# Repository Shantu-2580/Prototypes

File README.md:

<div align="center">

# ⚡ Prototypes

### Electronics • Embedded Systems • Robotics • PCB Design

*"Where ideas become circuits before they become products."*

</div>

---

# About

This repository contains my collection of hardware and embedded engineering prototypes.

Instead of polished end products, this repository documents experiments, PCB designs, robotics projects, firmware, and proof-of-concepts developed while exploring electronics and embedded systems.

Some projects are complete.

Some are works in progress.

Every project contributes to learning.

---

# Repository Structure

```text
Prototypes
│
├── ESP
│   │
│   ├── LM358_Audio_Input_Sensor
│   │   ├── KiCad PCB
│   │   ├── Schematic
│   │   └── Images
│   │
│   ├── Self_Balancing_Bot
│   │   ├── PCB
│   │   ├── Schematic
│   │   └── Arduino Code
│   │
│   ├── controller_sense
│   │   ├── Physical Controller Test
│   │   └── Virtual Controller Test
│   │
│   └── nexus_mascot_codes
│       └── Arduino Sketch
│
└── More prototypes coming soon...
```

---

# Current Projects

## 🎵 LM358 Audio Input Sensor

Custom PCB designed in KiCad for audio signal sensing using the LM358 operational amplifier.

**Includes**

- PCB Design
- Schematic
- Project Files
- Hardware Images
- Prototype Video

---

## 🤖 Self Balancing Bot

A robotics prototype focused on balancing algorithms and embedded control.

**Includes**

- KiCad PCB
- Circuit Schematic
- Arduino Firmware
- Project Files

---

## 🎮 Controller Sense

Python utilities for testing controller inputs.

Includes both:

- Physical controller testing
- Virtual controller simulation

---

## 🛰️ NEXUS Mascot

Arduino sketches related to the NEXUS mascot prototype.

---

# Tools Used

- KiCad
- Arduino IDE
- ESP32 / Arduino
- Python
- Git

---

# Philosophy

Every finished project begins as an experiment.

This repository serves as my engineering notebook where ideas are explored, validated, and improved before becoming complete systems.

---

# Roadmap

Future additions may include:

- ESP32 Projects
- IoT Systems
- PCB Designs
- Robotics
- Embedded AI
- Sensor Networks
- Control Systems
- Hardware Testing Utilities

---

# Contributing

Suggestions, improvements, and discussions are always welcome.

Feel free to open an Issue or submit a Pull Request.

---

<div align="center">

**Designed & Maintained by**

### Shantanu Gaikwad

*"Build. Test. Iterate. Repeat."*

⭐ If you find these projects useful, consider starring the repository.

</div>

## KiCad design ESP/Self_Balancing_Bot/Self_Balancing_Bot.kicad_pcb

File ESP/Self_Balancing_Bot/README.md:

# Self-Balancing Bot

A two-wheeled self-balancing robot using ESP32, MPU6050 (accelerometer + gyroscope), TB6612FNG motor driver, and Bluetooth gamepad control via Bluepad32.

## Hardware Requirements

| Component | Notes |
|-----------|-------|
| ESP32 DevKit | 30+ GPIO pins |
| MPU6050 | I2C address 0x68 (SDA=21, SCL=22) |
| TB6612FNG | Dual H-bridge motor driver |
| 2x DC Motors | With encoder support (optional) |
| LiPo Battery | 2S-3S (7.4V-11.1V) with voltage regulator |
| Bluetooth Gamepad | Tested with Xbox/PS4/8BitDo controllers |

## Pinout

```
ESP32          TB6612FNG          MPU6050
────────────────────────────────────────────
GPIO 33   →    PWMA
GPIO 14   →    AIN1
GPIO 15   →    AIN2
GPIO 32   →    PWMB
GPIO 26   →    BIN1
GPIO 27   →    BIN2
GPIO 21   →    SDA
GPIO 22   →    SCL
3.3V      →    VCC
GND       →    GND
```

## Firmware Files

### `Codes/P1/P1.ino` — Original Version
**Status:** Reference implementation (has placeholder values)

**Features:**
- Basic PID balance control (100Hz loop)
- Complementary filter for sensor fusion (MPU6050 accel + gyro)
- Bluetooth gamepad control via Bluepad32
- TB6612FNG motor driver interface
- Fall detection safety cutoff (>45°)

**Known Issues:**
- ❌ `Kp`, `Ki`, `Kd`, `base_setpoint` set to `Add_Values_Later` — **won't compile**
- ❌ No calibration routine — `base_setpoint` must be manually tuned per robot
- ❌ No integral anti-windup — causes overshoot after disturbances
- ❌ No motor deadband compensation — motors stall at low PWM
- ❌ No gamepad deadzone — joystick drift causes unwanted movement
- ❌ No controller watchdog — robot keeps moving if controller dies
- ❌ No MPU6050 verification — silent failure if sensor disconnected
- ❌ No serial telemetry — blind PID tuning

---

### `Codes/P1/Program2.ino` — Optimized Version
**Status:** Production-ready with all fixes

**All Original Features Plus:**

| Category | Improvements |
|----------|--------------|
| **Compilable** | Real PID defaults: `Kp=25.0`, `Ki=0.8`, `Kd=1.2` |
| **Calibration** | 2-second startup routine averages accelerometer to find `base_setpoint` automatically |
| **Anti-Windup** | Dual protection: integral clamped at ±400 + integration pauses when output saturates (±255) |
| **Motor Deadband** | `MIN_PWM=25` ensures TB6612FNG overcomes static friction |
| **Gamepad Deadzone** | Ignores joystick input < 20 (prevents center drift) |
| **Watchdog** | Auto-stops motors if controller disconnects >500ms |
| **Sensor Verify** | Checks WHO_AM_I register (0x68) at startup, halts if missing |
| **DLPF Config** | Hardware low-pass filter set to 44Hz (accel) / 42Hz (gyro) |
| **Telemetry** | 1Hz serial output: angle, setpoint, PID terms for tuning |
| **I2C Optimized** | Single 14-byte read transaction per loop |

---

## PID Tuning Guide (Program2)

Open Serial Monitor at **115200 baud**. You'll see:
```
Angle: 0.12 | Setpoint: 0.00 | Out: -15.3 | P: -3.0 I: -0.2 D: -12.1
```

### Tuning Order:
1. **Kp only** (set `Ki=0, Kd=0`): Increase until sustained oscillation, then reduce ~30%
2. **Kd**: Add to dampen oscillations (start ~0.5-2.0)
3. **Ki**: Small value (0.5-2.0) to eliminate steady-state drift

### Tips:
- Hold robot upright during 2-second calibration (LED on ESP32 blinks during this)
- Test on carpet first — smoother surface = easier balance
- If robot falls backward consistently, increase `base_setpoint` slightly (or add weight forward)
- `Kp` typically 20-50, `Kd` 0.5-3, `Ki` 0.5-2 for this hardware

---

## Building & Flashing

### Arduino IDE
1. Install ESP32 board package: `https://dl.espressif.com/dl/package_esp32_index.json`
2. Install **Bluepad32** library via Library Manager
3. Open `Program2.ino`, select board **ESP32 Dev Module**, upload

### PlatformIO (Recommended)
```ini
; platformio.ini
[env:esp32dev]
platform = espressif32
board = esp32dev
framework = arduino
lib_deps =
    ricardoquesada/Bluepad32 @ ^2.0.0
monitor_speed = 115200
```

---

## Troubleshooting

| Symptom | Likely Cause | Fix |
|---------|--------------|-----|
| Won't compile | Using `P1.ino` | Use `Program2.ino` |
| Falls immediately | PID not tuned | Follow tuning guide above |
| Drifts forward/back | Wrong `base_setpoint` | Re-calibrate (reset ESP32) |
| Oscillates violently | Kp too high / Kd too low | Reduce Kp, increase Kd |
| Slow to correct | Kp too low | Increase Kp |
| Motors hum but don't turn | Deadband too low | Increase `MIN_PWM` (try 30-40) |
| Controller doesn't pair | Bluepad32 keys stored | `BP32.forgetBluetoothKeys()` runs on startup |
| MPU6050 not detected | Wiring / I2C address | Check SDA/SCL, try 0x69 (AD0=HIGH) |

---

## License

MIT — Feel free to use, modify, distribute.

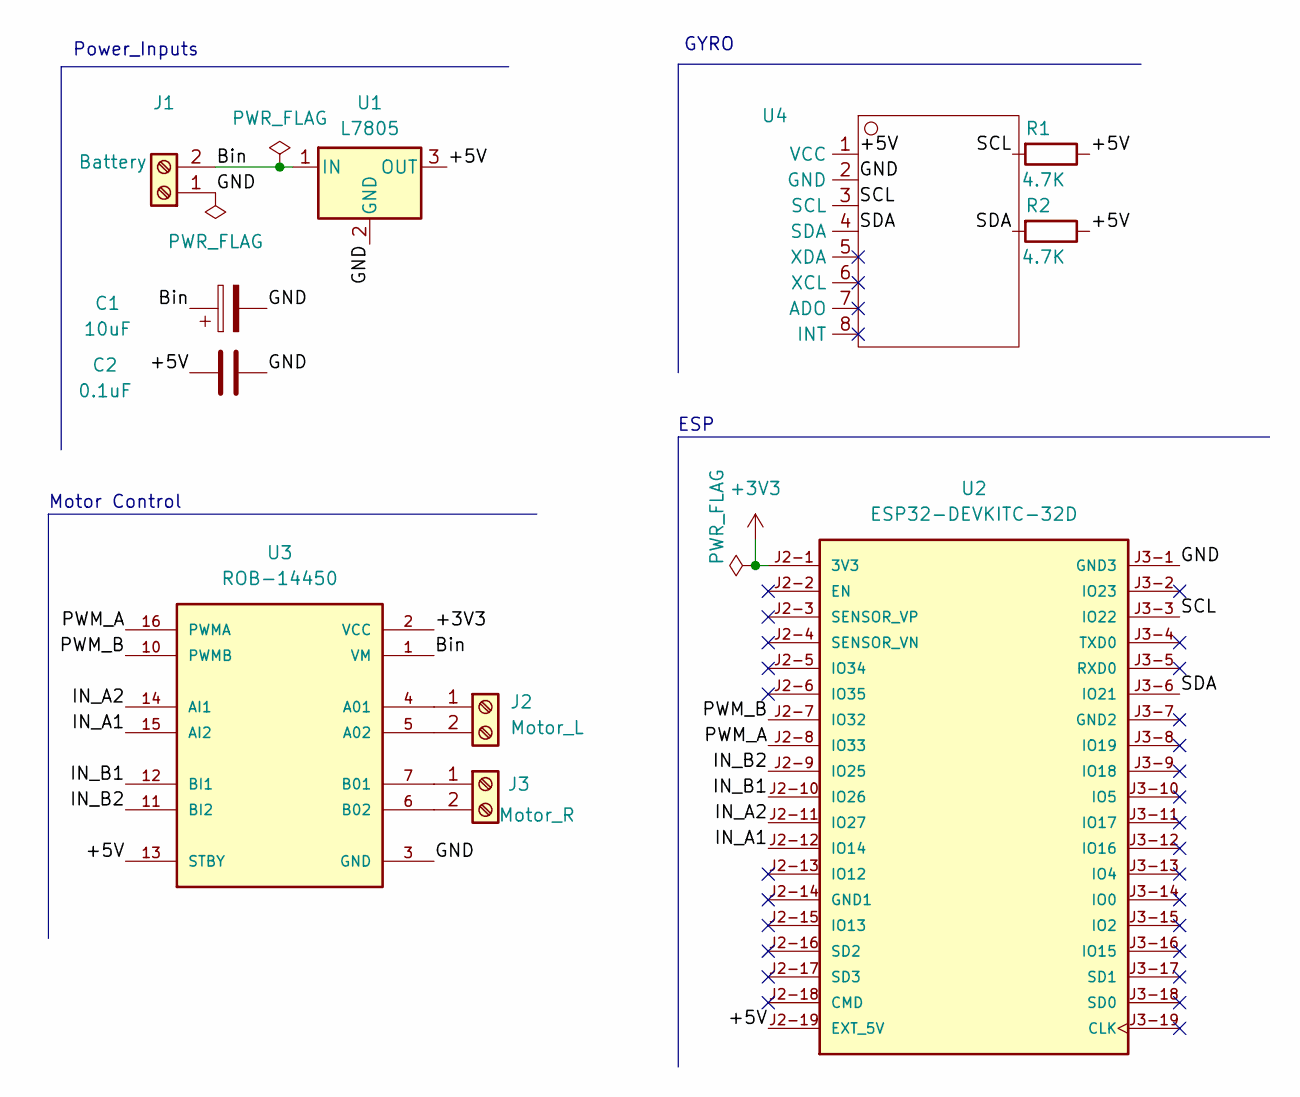
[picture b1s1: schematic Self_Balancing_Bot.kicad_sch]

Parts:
C1: 10uF; CP_Radial_D5.0mm_P2.00mm
C2: 0.1uF; CP_Radial_D5.0mm_P2.50mm
J1: Battery; PhoenixContact_MSTBA_2,5_2-G-5,08_1x02_P5.08mm_Horizontal
J2: Motor_L; PhoenixContact_MSTBA_2,5_2-G-5,08_1x02_P5.08mm_Horizontal
J3: Motor_R; PhoenixContact_MSTBA_2,5_2-G-5,08_1x02_P5.08mm_Horizontal
R1, R2: 4.7K; R_Axial_DIN0207_L6.3mm_D2.5mm_P7.62mm_Horizontal
U1: L7805; TO-220-3_Vertical
U2: ESP32-DEVKITC-32D; MODULE_ESP32-DEVKITC-32D; PARTREV V4
U3: ROB-14450; MODULE_ROB-14450; PARTREV 11-13-17
U4: Untitled

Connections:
+3V3: U2.J2-1 (3V3), U3.2 (VCC)
/+5V: C2.1, R1.1, R2.1, U1.3 (OUT), U2.J2-19 (EXT_5V), U3.13 (STBY), U4.1 (VCC)
/Bin: C1.1, J1.2, U1.1 (IN), U3.1 (VM)
/IN_A1: U2.J2-12 (IO14), U3.15 (AI2)
/IN_A2: U2.J2-11 (IO27), U3.14 (AI1)
/IN_B1: U2.J2-10 (IO26), U3.12 (BI1)
/IN_B2: U2.J2-9 (IO25), U3.11 (BI2)
/PWM_A: U2.J2-8 (IO33), U3.16 (PWMA)
/PWM_B: U2.J2-7 (IO32), U3.10 (PWMB)
/SCL: R1.2, U2.J3-3 (IO22), U4.3 (SCL)
/SDA: R2.2, U2.J3-6 (IO21), U4.4 (SDA)
GND: C1.2, C2.2, J1.1, U1.2 (GND), U2.J3-1 (GND3), U3.3 (GND), U3.8 (GND), U3.9 (GND), U4.2 (GND)
unnamed: J2.1, U3.4 (A01)
unnamed: J2.2, U3.5 (A02)
unnamed: J3.1, U3.7 (B01)
unnamed: J3.2, U3.6 (B02)

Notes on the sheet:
GYRO
ESP
Motor Control
Power_Inputs

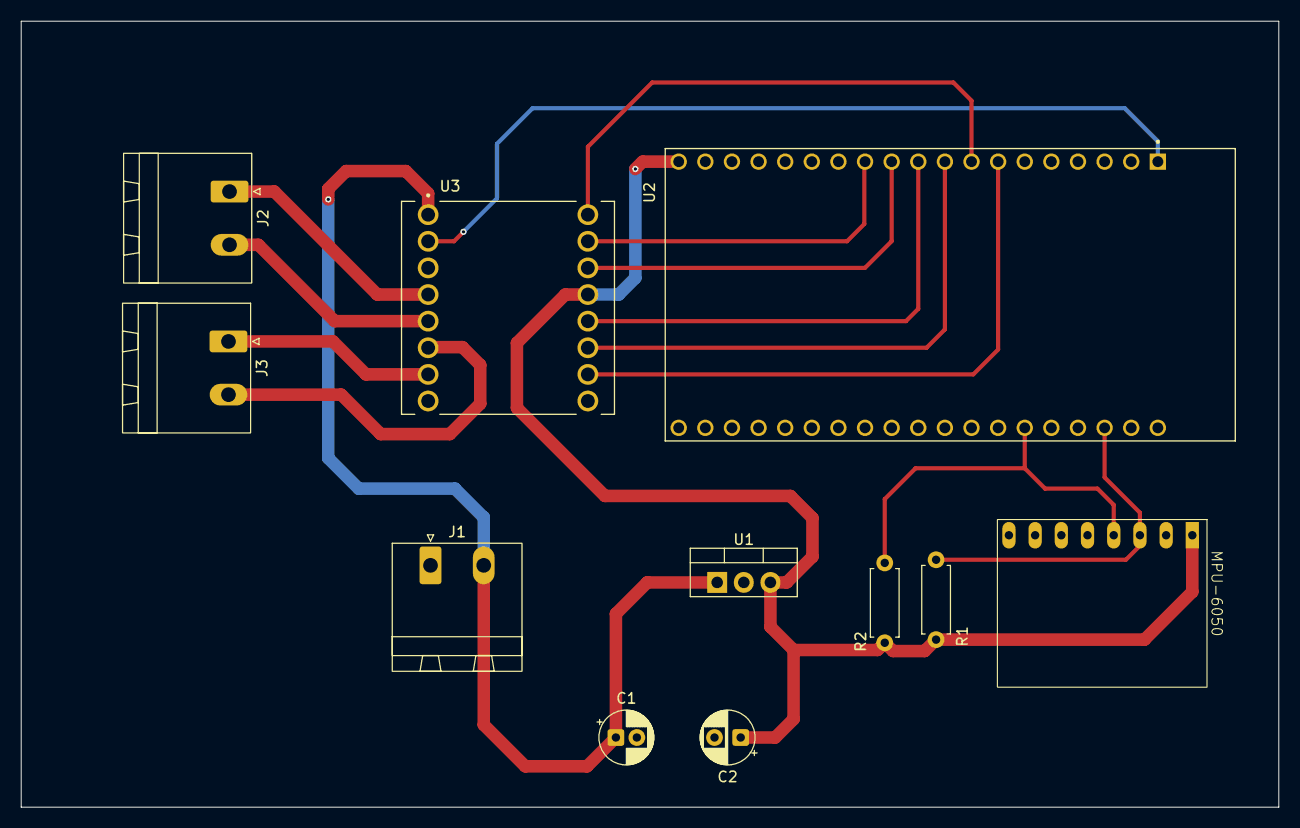
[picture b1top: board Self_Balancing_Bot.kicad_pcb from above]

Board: 2 copper layers, 120.0 x 75.0 mm, 11 parts (0 on the bottom side), 16 nets.

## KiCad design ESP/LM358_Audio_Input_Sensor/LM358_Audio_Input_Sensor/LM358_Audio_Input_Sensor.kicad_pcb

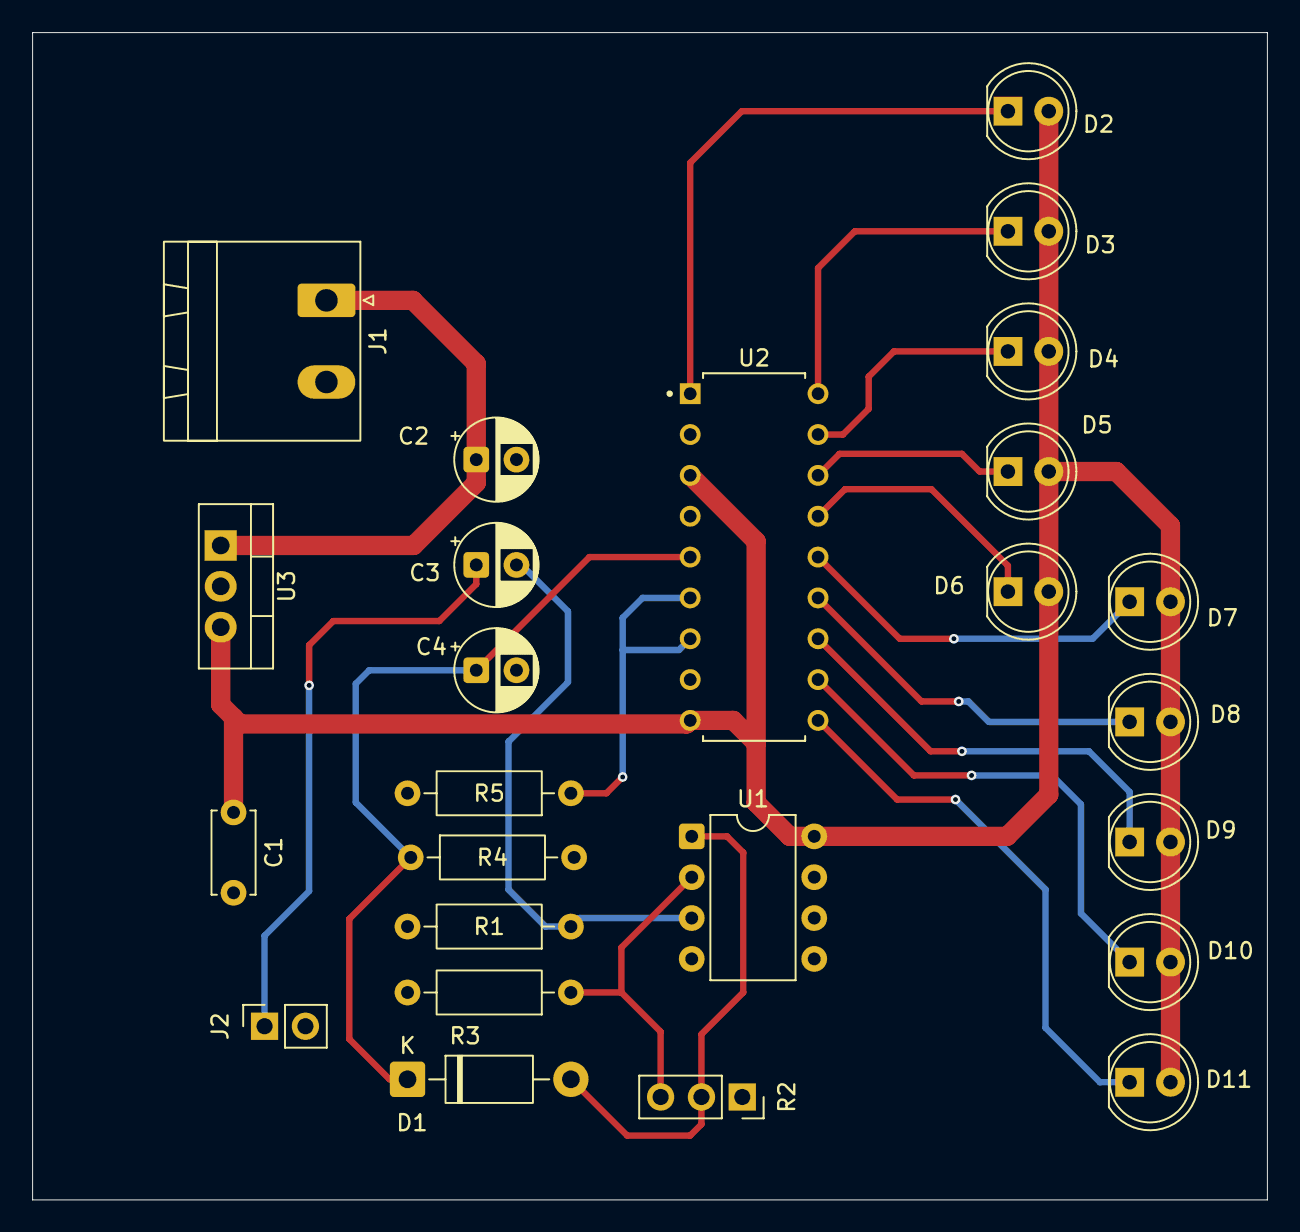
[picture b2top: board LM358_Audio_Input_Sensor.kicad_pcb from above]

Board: 2 copper layers, 76.8 x 72.6 mm, 25 parts (0 on the bottom side), 19 nets.

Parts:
C1: 100nF; C_Disc_D5.0mm_W2.5mm_P5.00mm
C2: 10uF; CP_Radial_D5.0mm_P2.50mm
C3, C4: 1uF; CP_Radial_D5.0mm_P2.50mm
D1: 1N4007; D_DO-41_SOD81_P10.16mm_Horizontal
D2, D3, D4, D5, D6, D7, D8, D9, D10, D11: LED; LED_D5.0mm
J1: Battery_in; PhoenixContact_MSTBA_2,5_2-G-5,08_1x02_P5.08mm_Horizontal
J2: Audio_in; PinSocket_1x02_P2.54mm_Vertical
R1, R3: 100k; R_Axial_DIN0207_L6.3mm_D2.5mm_P10.16mm_Horizontal
R2: Potentiometer; PinSocket_1x03_P2.54mm_Vertical
R4: 10k; R_Axial_DIN0207_L6.3mm_D2.5mm_P10.16mm_Horizontal
R5: 1.2k; R_Axial_DIN0207_L6.3mm_D2.5mm_P10.16mm_Horizontal
U1: DIP-8_W7.62mm
U2: LM3915; DIP795W45P254L2286H533Q18B
U3: L7805; TO-220-3_Vertical

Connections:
/+5V: C1.1, D2.2 (A), D3.2 (A), D4.2 (A), D5.2 (A), D6.2 (A), D7.2 (A), D8.2 (A), D9.2 (A), D10.2 (A), D11.2 (A), U1.8 (+Vcc), U2.3 (V+), U2.9 (MODE_SELECT), U3.3 (OUT)
/Fo: C4.1, D1.1 (K), R4.1, U2.5 (SIGNAL_INPUT)
/GND: C1.2, C2.2, C4.2, J1.2, J2.2, R1.2, R3.2, R4.2, R5.2, U1.4 (-VDD), U2.2 (V-), U2.4 (DIVIDER(LOW_END)), U2.8 (REFERENCE_ADJUST), U3.2 (GND)
/O1: D1.2 (A), R2.2, U1.1 (Out1)
unnamed: D2.1 (K), U2.1 (LED1)
unnamed: D3.1 (K), U2.18 (LED2)
unnamed: D4.1 (K), U2.17 (LED3)
unnamed: D5.1 (K), U2.16 (LED4)
unnamed: D6.1 (K), U2.15 (LED5)
unnamed: D7.1 (K), U2.14 (LED6)
unnamed: D8.1 (K), U2.13 (LED7)
unnamed: D9.1 (K), U2.12 (LED8)
unnamed: D10.1 (K), U2.11 (LED9)
unnamed: D11.1 (K), U2.10 (LED10)
unnamed: C2.1, J1.1, U3.1 (IN)
unnamed: C3.1, J2.1
unnamed: C3.2, R1.1, U1.3 (+In1)
unnamed: R2.3, R3.1, U1.2 (-In1)
unnamed: R5.1, U2.6 (DIVIDER(HIGH_END)), U2.7 (REFERENCE_OUTPUT)

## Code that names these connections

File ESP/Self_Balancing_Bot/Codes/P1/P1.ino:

#include <Wire.h>          // I2C communication library (used for MPU6050)
#include <Bluepad32.h>    // Bluetooth game controller library

// ==========================================
// CONTROLLER CONFIG
// Handles gamepad connection and movement input
// movementOffset → dynamically shifts robot tilt to move forward/backward
// ==========================================
GamepadPtr myGamepad = nullptr;
float movementOffset = 0.0;
const float maxOffset = 5.0;  // Maximum tilt angle shift for movement

// ==========================================
// PIN DEFINITIONS
// Maps ESP32 GPIO pins to motor driver (TB6612FNG)
// PWM pins control speed, IN pins control direction
// ==========================================
#define PIN_PWM_A  33
#define PIN_IN_A1  14
#define PIN_IN_A2  15

#define PIN_PWM_B  32
#define PIN_IN_B1  26
#define PIN_IN_B2  27

// ==========================================
// PID PARAMETERS
// Core control system constants
// These determine how aggressively the robot balances
// ==========================================
double Kp = Add_Values_Later   // Proportional gain → reacts to tilt error
double Ki = Add_Values_Later  // Integral gain → corrects long-term drift
double Kd = Add_Values_Later   // Derivative gain → reduces oscillations

double base_setpoint = Add_Values_Later  // Default upright angle
double setpoint;              // Final target tilt (adjusted via controller)
double input, output;
double error, lastError, cumulativeError;

// ==========================================
// FILTER & TIMING
// Handles sensor fusion and loop timing
// dt → fixed loop interval (100Hz)
// alpha → complementary filter blending factor
// ==========================================
unsigned long lastTime;
const double dt = 0.01;
double robotAngle = 0.0;
const double alpha = 0.96;

const int MPU_addr = 0x68;  // I2C address of MPU6050

// ==========================================
// GAMEPAD CALLBACKS
// Automatically triggered when controller connects/disconnects
// ==========================================
void onConnectedGamepad(GamepadPtr gp) {
myGamepad = gp;  // Store active controller reference
}

void onDisconnectedGamepad(GamepadPtr gp) {
myGamepad = nullptr;  // Clear controller reference
}

// ==========================================
// SETUP FUNCTION
// Runs once at startup
// Initializes Serial, I2C, motors, MPU6050, and Bluetooth controller
// ==========================================
void setup() {
Serial.begin(115200);
Wire.begin(21, 22);  // Initialize I2C (SDA = 21, SCL = 22)

// Configure motor driver pins as outputs
pinMode(PIN_PWM_A, OUTPUT);
pinMode(PIN_IN_A1, OUTPUT);
pinMode(PIN_IN_A2, OUTPUT);
pinMode(PIN_PWM_B, OUTPUT);
pinMode(PIN_IN_B1, OUTPUT);
pinMode(PIN_IN_B2, OUTPUT);

// Wake up MPU6050 (disable sleep mode)
Wire.beginTransmission(MPU_addr);
Wire.write(0x6B);
Wire.write(0);
Wire.endTransmission(true);

// Initialize Bluetooth controller handling
BP32.setup(&onConnectedGamepad, &onDisconnectedGamepad);
BP32.forgetBluetoothKeys();  // Allows new pairing

lastTime = millis();
}

// ==========================================
// MAIN LOOP
// Runs continuously
// Handles controller input + executes control loop at 100Hz
// ==========================================
void loop() {
BP32.update();  // Update controller state

// ======================================
// CONTROLLER INPUT PROCESSING
// Converts joystick input into tilt offset
// ======================================
if (myGamepad && myGamepad->isConnected()) {
int yAxis = myGamepad->axisY();  // Forward/backward input

```
// Map joystick range (-512 to 512) → tilt offset
movementOffset = (float)yAxis / 512.0 * maxOffset;
```

} else {
movementOffset = 0;  // No controller → stay balanced
}

// Final setpoint = base tilt + user input
setpoint = base_setpoint + movementOffset;

// ======================================
// TIMED CONTROL LOOP (100Hz)
// Ensures stable and consistent PID execution
// ======================================
unsigned long currentTime = millis();
if (currentTime - lastTime >= 10) {
readSensorData();   // Get current tilt
calculatePID();     // Compute correction
driveMotors();      // Apply correction


lastTime = currentTime;


}
}

// ==========================================
// SENSOR DATA ACQUISITION
// Reads MPU6050 accelerometer + gyroscope
// Applies complementary filter to estimate tilt angle
// ==========================================
void readSensorData() {
int16_t AcX, AcY, AcZ, GyX;

// Request sensor data from MPU6050
Wire.beginTransmission(MPU_addr);
Wire.write(0x3B);
Wire.endTransmission(false);
Wire.requestFrom((uint8_t)MPU_addr, (size_t)14, (bool)true);

// Read accelerometer values
AcX = Wire.read() << 8 | Wire.read();
AcY = Wire.read() << 8 | Wire.read();
AcZ = Wire.read() << 8 | Wire.read();

Wire.read() << 8 | Wire.read();  // Skip temperature

// Read gyroscope value
GyX = Wire.read() << 8 | Wire.read();

// Convert accelerometer data to angle
double accAngle = atan2((double)AcY, (double)AcZ) * 57.2958;

// Convert gyro data to angular velocity
double gyroRate = (double)GyX / 131.0;

// Complementary filter:
// Combines fast gyro response + stable accel reading
robotAngle = alpha * (robotAngle + gyroRate * dt) + (1.0 - alpha) * accAngle;

input = robotAngle;  // Input to PID controller
}

// ==========================================
// PID CONTROL LOGIC
// Computes correction required to maintain balance
// ==========================================
void calculatePID() {
error = input - setpoint;

// Proportional term → reacts to current tilt
double pTerm = Kp * error;

// Integral term → accumulates past error
cumulativeError += error * dt;
cumulativeError = constrain(cumulativeError, -400.0, 400.0);
double iTerm = Ki * cumulativeError;

// Derivative term → predicts future trend
double dTerm = Kd * ((error - lastError) / dt);

// Total PID output
output = pTerm + iTerm + dTerm;
lastError = error;

// Limit output to motor PWM range
output = constrain(output, -255.0, 255.0);
}

// ==========================================
// MOTOR CONTROL
// Converts PID output into motor speed + direction
// ==========================================
void driveMotors() {
int motorSpeed = abs((int)output);

// Safety: stop motors if robot falls too much
if (abs(robotAngle) > 45.0) {
analogWrite(PIN_PWM_A, 0);
analogWrite(PIN_PWM_B, 0);
return;
}

// Direction control based on tilt correction
if (output > 0) {
// Move forward
digitalWrite(PIN_IN_A1, HIGH);
digitalWrite(PIN_IN_A2, LOW);
digitalWrite(PIN_IN_B1, HIGH);
digitalWrite(PIN_IN_B2, LOW);
} else {
// Move backward
digitalWrite(PIN_IN_A1, LOW);
digitalWrite(PIN_IN_A2, HIGH);
digitalWrite(PIN_IN_B1, LOW);
digitalWrite(PIN_IN_B2, HIGH);
}

// Apply speed using PWM
analogWrite(PIN_PWM_A, motorSpeed);
analogWrite(PIN_PWM_B, motorSpeed);
}

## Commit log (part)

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2026-03-18 Controller updated
2026-03-19 added virtual setup for esp
2026-06-16 Adding my previous projects
    Adding my projects which were refined
2026-06-16 Added all the previous files and videos
